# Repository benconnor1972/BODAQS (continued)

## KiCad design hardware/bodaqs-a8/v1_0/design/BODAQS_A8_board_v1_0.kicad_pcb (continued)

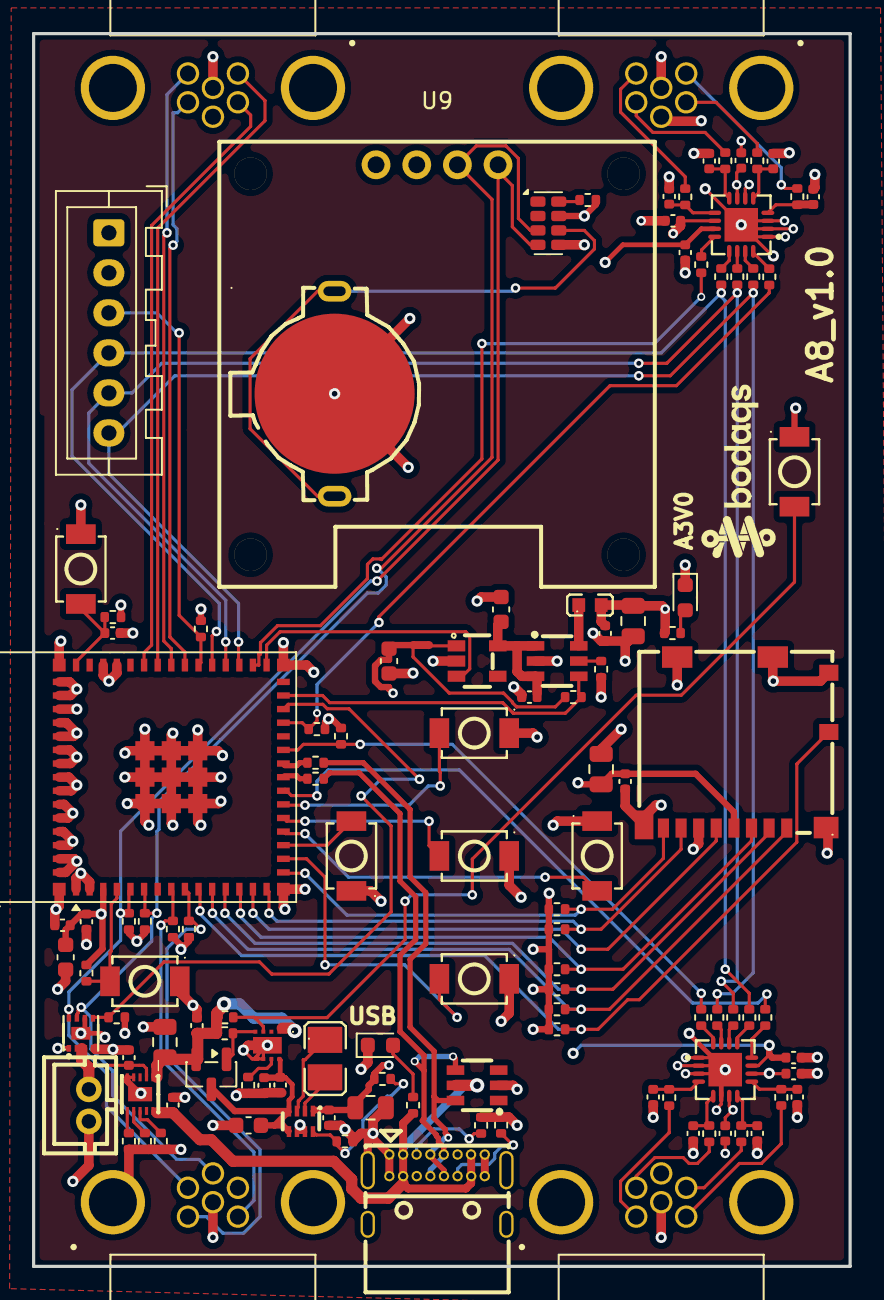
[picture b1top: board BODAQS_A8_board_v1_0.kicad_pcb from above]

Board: 4 copper layers, 51.0 x 77.0 mm, 120 parts (0 on the bottom side), 89 nets.

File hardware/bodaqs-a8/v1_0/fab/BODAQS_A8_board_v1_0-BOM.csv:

Designator,Footprint,Quantity,Value,LCSC Part #
BT1,BAT-TH_MY-1220-01,1,MY-1220-01,C964817
"C1, C10, C14, C15, C16, C18, C20, C29, C30, C31, C32, C7",0402,12,100nF,C1525
"C11, C33, C34, C6, C3",0402,4,1uF,C52923
"C12, C13",0603,2,2.2uF,C23630
"C17, C19, C9",0805,3,10uF,C15850
"C2, C8",0603,2,22uF,C84419
"C21, C22, C23, C24, C25, C26, C27, C28",0402,8,10nF,C15195
C4,0402,1,4.7uF,C23733
C5,0805,1,47uF,C16780
CN1,CONN-TH_B2B-PH-K-S,1,Battery,C131337
"D1, D2",0603,2,Red,C2286
IC1,XC6193AA05ERG,1,XC6193A103ER-G,C19267155
L1,L0603,1,MPZ1608S601ATA00,C107335
Q1,SOT-23,1,DMG2301L,C102619
"R1, R11, R13, R15, R22, R25, R26, R27, R28, R29, R30, R31, R4",0402,13,10k,C25744
"R10, R9",0402,2,22,C25092
R12,0402,1,511k,C64042
R14,0402,1,91k,C4147
R16,0402,1,18k,C25762
R17,0402,1,1k,C11702
"R18, R19, R3, R5, R7, R8",0402,6,4.7k,C25900
"R2, R6",0402,2,47k,C25792
"R20, R21, R23",0402,3,200k,C25764
R24,0402,1,133k,C25753
"R32, R33, R34, R35, R36, R37, R38, R39",0402,8,100R,C25076
"R40, R41, R42, R43, R44, R45, R46, R47, R48, R49",0402,10,47R,C25120
"R50, R51",0402,2,5.1k,C25905
SIM1,SIM-SMD_8P-1040310811,1,1040310811,C585350
"SW1, SW2, SW3, SW4, SW5, SW6, SW7, SW8",SW-SMD_L3.9-W3.0-P4.45,8,TS-1088-AR02016,C720477
U1,ESP32-S2-MINI-1,1,ESP32-S3-MINI,C3013941
"U10, U11",VQFN-16_L3.5-W3.5-P0.50-BL-EP2.1,2,ADS1220IRVAR,C2651338
U12,SOT-23-6_L2.9-W1.6-P0.95-LS2.8-BR,1,DT1042-04SO,C19626385
U2,L1008,1,DFE252012P-1R0M=P2,C882955
U3,TDFN-8_L2.0-W2.0-P0.50-BL-EP1.2,1,MAX17048G+T10,C2682616
U4,SOT-583-8_L2.1-W1.2-P0.50-LS1.6-BL,1,TPS631000DRLR,C5219190
U5,WSON-10_L2.2-W2.0-P0.40-BL-EP_TI_DLH0010A,1,BQ25185DLHR,C19725033
U6,TSOT-23-5_L2.9-W1.6-P0.95-LS2.8-BR,1,TPS7A2030PDBVR,C963429
U7,SOT-23-6_L2.9-W1.6-P0.95-LS2.8-BR,1,TPS2553DBVR,C55266
U8,MicroCrystal_C7_SON-8_1.5x3.2mm_P0.9mm,1,RV-3028-C7,C3019759
USB1,USC-C-SMD_USB4085-GF-A,1,USB4085-GF-A_C7095263,C7095263

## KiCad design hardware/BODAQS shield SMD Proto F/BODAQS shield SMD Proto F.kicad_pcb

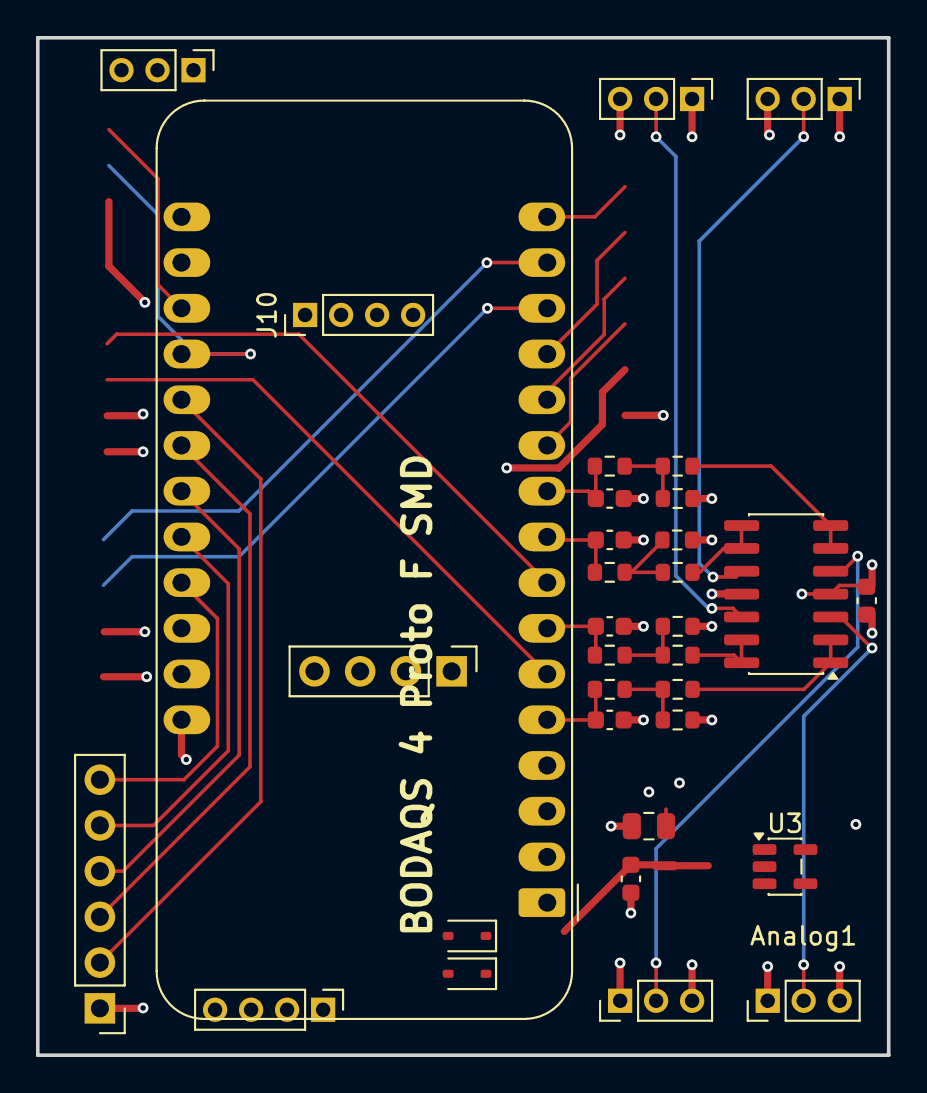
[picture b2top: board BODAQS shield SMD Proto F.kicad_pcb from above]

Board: 4 copper layers, 47.3 x 56.5 mm, 34 parts (0 on the bottom side), 37 nets.

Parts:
C2, C3, C5, C7: 10nF; C_0603_1608Metric
C9: 100nF; C_0603_1608Metric
C17: 2.2uF; C_0805_2012Metric
C21: 2.2uF; C_0603_1608Metric
D1, D2: BAT60A; D_SOD-323
J1: Analog1; PinHeader_1x03_P2.00mm_Vertical
J2: Analog2; PinHeader_1x03_P2.00mm_Vertical
J3: Analog3; PinHeader_1x03_P2.00mm_Vertical
J4: Analog4; PinHeader_1x03_P2.00mm_Vertical
J5: Bar; PinHeader_1x03_P2.00mm_Vertical
J6: I2C1; PinHeader_1x04_P2.00mm_Vertical
J7: UART; PinHeader_1x04_P2.54mm_Vertical
J8: Navigation; PinHeader_1x06_P2.54mm_Vertical
J10: I2C0; PinHeader_1x04_P2.00mm_Vertical
NT1: NetTie_2; NetTie-2_SMD_Pad0.5mm
R1, R4, R6, R8, R9, R10, R11, R12: 10K; R_0603_1608Metric
R2, R3, R5, R7: 68R; R_0603_1608Metric
U1: Adafruit_Feather
U2: MCP6004; SOIC-14_3.9x8.7mm_P1.27mm
U3: TPS7A2033PDBVR; SOT-23-5

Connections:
LED: J5.3, U1.19 (GPIO1)
TXO: J7.4, U1.15 (43/TX)
+3V3: J6.2, J7.1, J10.2, U1.2 (3.3V)
A3V3: C9.1, C17.1, J1.1, J2.1, J3.1, J4.1, U2.4 (V+), U3.5 (OUT)
ANALOG1: C2.1, R2.1, U1.5 (10/AN)
ANALOG2: C3.1, R3.1, U1.10 (18/AN)
ANALOG3: C5.1, R5.1, U1.9 (17/AN)
ANALOG4: C7.1, R7.1, U1.7 (15/AN)
Down: J8.5, U1.24 (GPIO7)
EN: U1.16 (GPIO42), U3.3 (EN)
Enter: J8.2, U1.21 (GPIO4)
GND: C2.2, C3.2, C5.2, C7.2, C9.2, C17.2, C21.2, J1.3, J2.3, J3.3, J4.3, J5.1, J6.1, J7.2, J8.1, J10.1, R9.1, R10.1, R11.1, R12.1, U1.4 (GND), U2.11 (V-), U3.2 (GND)
Left: J8.4, U1.23 (GPIO6)
Mark: J5.2, U1.20 (GPIO2)
unnamed: J1.2, U2.3 (+)
unnamed: J2.2, U2.5 (+)
unnamed: J3.2, U2.10 (+)
unnamed: J4.2, U2.12 (+)
unnamed: R1.1, R2.2, R9.2
unnamed: R3.2, R4.1, R10.2
unnamed: R5.2, R6.1, R11.2
unnamed: R7.2, R8.1, R12.2
unnamed: R1.2, U2.1, U2.2 (-)
unnamed: R4.2, U2.6 (-), U2.7
unnamed: R6.2, U2.8, U2.9 (-)
unnamed: R8.2, U2.13 (-), U2.14
unnamed: NT1.2, U3.1 (IN)
RXI: J7.3, U1.14 (44/RX)
Right: J8.3, U1.22 (GPIO5)
SCL0: J10.3, U1.18 (SCL/9)
SCL1: J6.3, U1.6 (14/AN)
SDA0: J10.4, U1.17 (SDA/8)
SDA1: J6.4, U1.8 (16/AN)
Up: J8.6, U1.25 (GPIO21)
VBAT: D1.2 (A), U1.28 (VBAT)
VIN: C21.1, D1.1 (K), D2.1 (K), NT1.1
VUSB: D2.2 (A), U1.26 (VUSB)

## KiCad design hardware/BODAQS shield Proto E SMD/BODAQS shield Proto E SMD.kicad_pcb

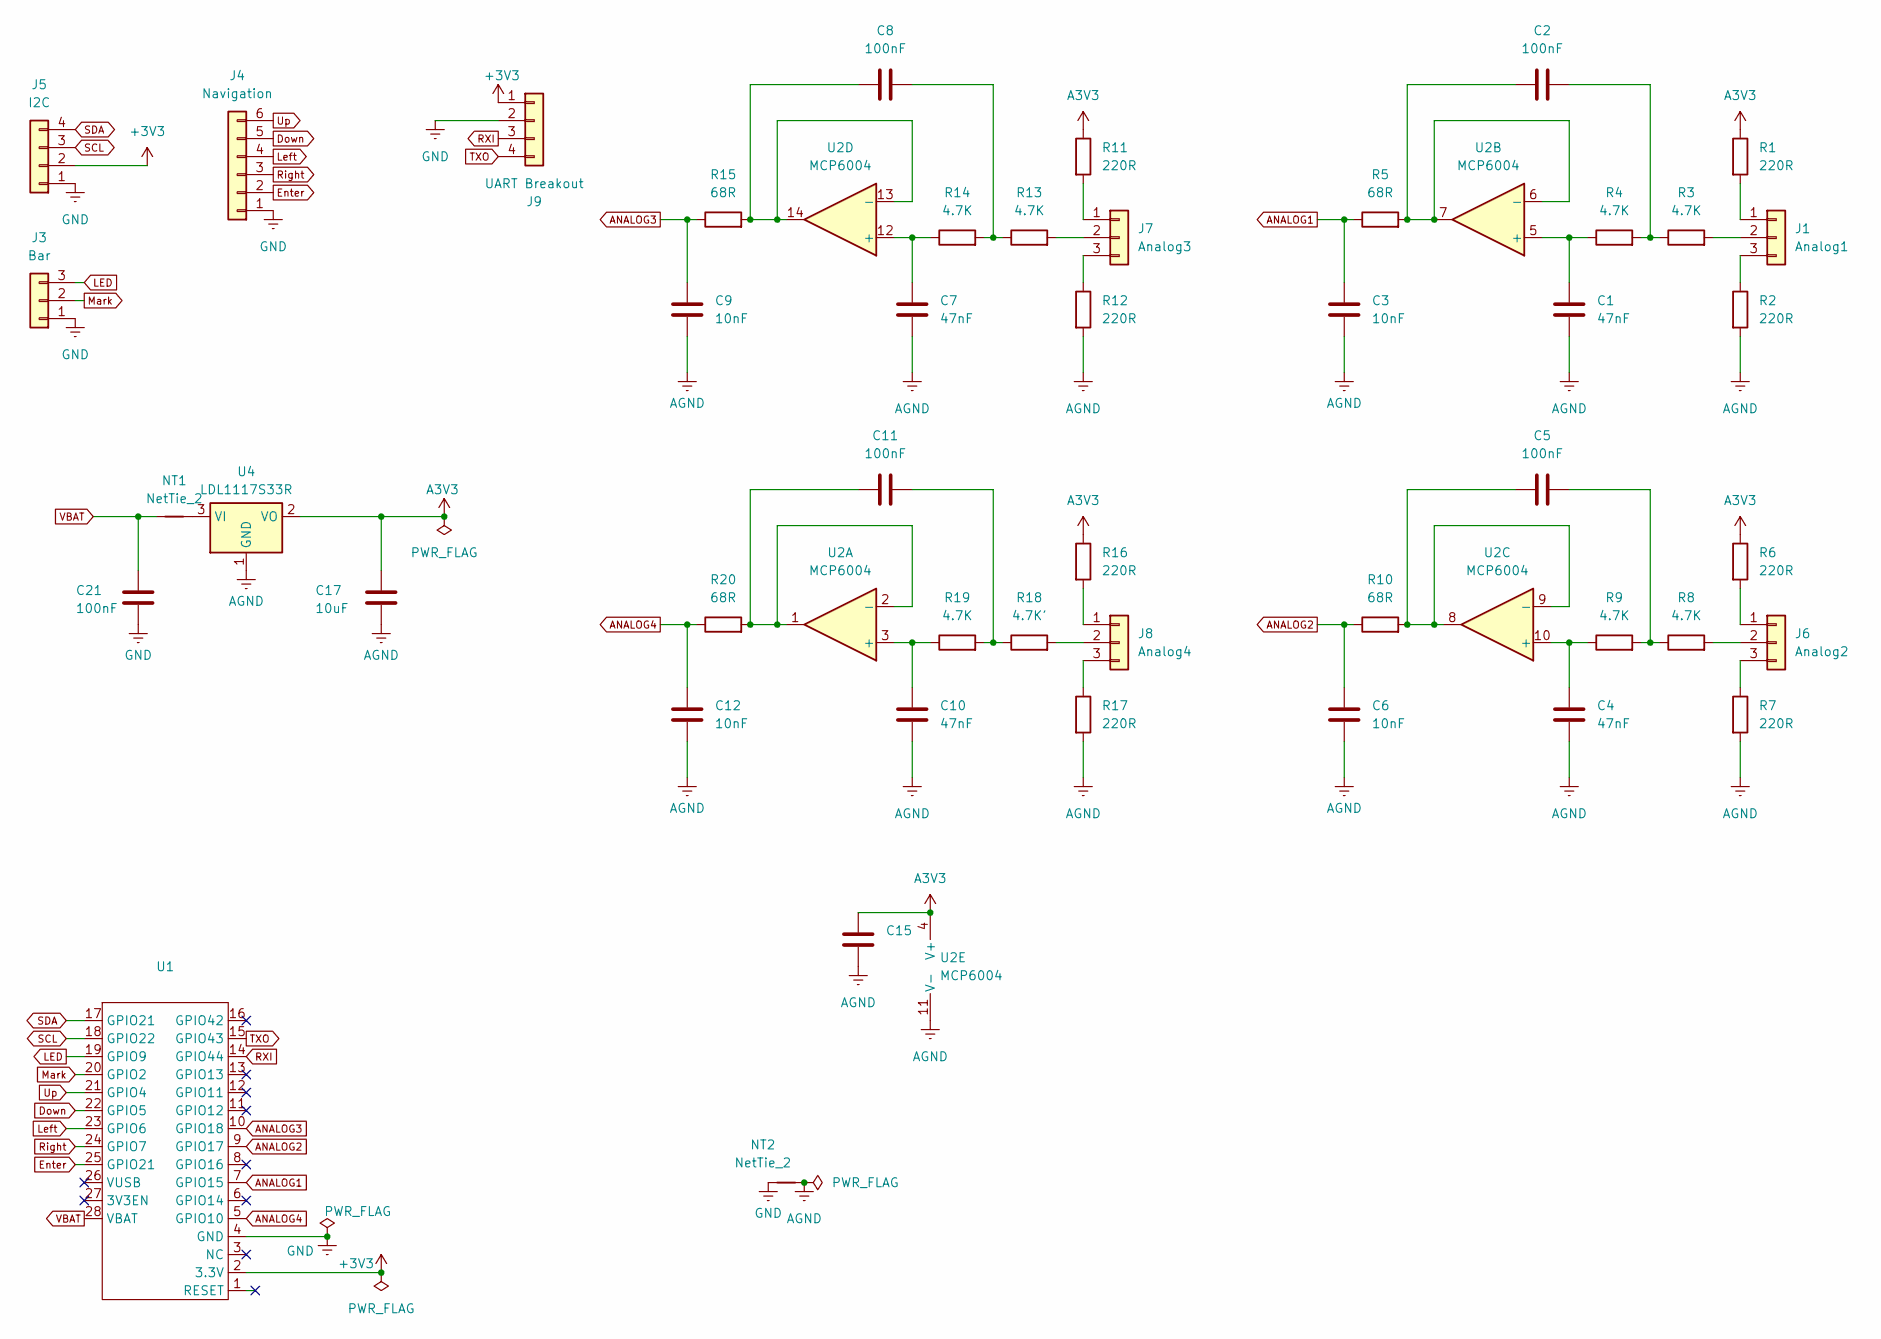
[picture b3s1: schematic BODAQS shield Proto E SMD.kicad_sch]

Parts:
C1, C4, C7, C10: 47nF; C_0603_1608Metric
C2, C5, C8, C11, C15, C21: 100nF; C_0603_1608Metric
C3, C6, C9, C12: 10nF; C_0603_1608Metric
C17: 10uF; C_0805_2012Metric
J1: Analog1; PinHeader_1x03_P2.00mm_Vertical
J3: Bar; PinHeader_1x03_P2.00mm_Vertical
J4: Navigation; PinHeader_1x06_P2.54mm_Vertical
J5: I2C; PinHeader_1x04_P2.00mm_Vertical
J6: Analog2; PinHeader_1x03_P2.00mm_Vertical
J7: Analog3; PinHeader_1x03_P2.00mm_Vertical
J8: Analog4; PinHeader_1x03_P2.00mm_Vertical
J9: UART Breakout; PinHeader_1x04_P2.54mm_Vertical
NT1, NT2: NetTie_2; NetTie-2_SMD_Pad0.5mm
R1, R2, R6, R7, R11, R12, R16, R17: 220R; R_0603_1608Metric
R3, R4, R8, R9, R13, R14, R19: 4.7K; R_0603_1608Metric
R5, R10, R15, R20: 68R; R_0603_1608Metric
R18: 4.7K'; R_0603_1608Metric
U1: Adafruit_Feather
U2: MCP6004; SOIC-14_3.9x8.7mm_P1.27mm
U4: LDL1117S33R; SOT-223-3_TabPin2

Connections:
LED: J3.3, U1.19 (GPIO9)
TXO: J9.4, U1.15 (GPIO43)
+3V3: J5.2, J9.1, U1.2 (3.3V)
A3V3: C15.1, C17.1, R1.1, R6.1, R11.1, R16.1, U2.4 (V+), U4.2 (VO)
AGND: C1.2, C3.2, C4.2, C6.2, C7.2, C9.2, C10.2, C12.2, C15.2, C17.2, NT2.2, R2.2, R7.2, R12.2, R17.2, U2.11 (V-), U4.1 (GND)
ANALOG1: C3.1, R5.1, U1.7 (GPIO15)
ANALOG2: C6.1, R10.1, U1.9 (GPIO17)
ANALOG3: C9.1, R15.1, U1.10 (GPIO18)
ANALOG4: C12.1, R20.1, U1.5 (GPIO10)
Down: J4.5, U1.22 (GPIO5)
Enter: J4.2, U1.25 (GPIO21)
GND: C21.2, J3.1, J4.1, J5.1, J9.2, NT2.1, U1.4 (GND)
Left: J4.4, U1.23 (GPIO6)
Mark: J3.2, U1.20 (GPIO2)
unnamed: C2.2, R3.1, R4.2
unnamed: C5.2, R8.1, R9.2
unnamed: C8.2, R13.1, R14.2
unnamed: C11.2, R18.1, R19.2
unnamed: J1.1, R1.2
unnamed: J1.2, R3.2
unnamed: J1.3, R2.1
unnamed: J6.1, R6.2
unnamed: J6.2, R8.2
unnamed: J6.3, R7.1
unnamed: J7.1, R11.2
unnamed: J7.2, R13.2
unnamed: J7.3, R12.1
unnamed: J8.1, R16.2
unnamed: J8.2, R18.2
unnamed: J8.3, R17.1
unnamed: C10.1, R19.1, U2.3 (+)
unnamed: C11.1, R20.2, U2.1, U2.2 (-)
unnamed: C1.1, R4.1, U2.5 (+)
unnamed: C2.1, R5.2, U2.6 (-), U2.7
unnamed: C4.1, R9.1, U2.10 (+)
unnamed: C5.1, R10.2, U2.8, U2.9 (-)
unnamed: C7.1, R14.1, U2.12 (+)
unnamed: C8.1, R15.2, U2.13 (-), U2.14
unnamed: NT1.2, U4.3 (VI)
RXI: J9.3, U1.14 (GPIO44)
Right: J4.3, U1.24 (GPIO7)
SCL: J5.3, U1.18 (GPIO22)
SDA: J5.4, U1.17 (GPIO21)
Up: J4.6, U1.21 (GPIO4)
VBAT: C21.1, NT1.1, U1.28 (VBAT)

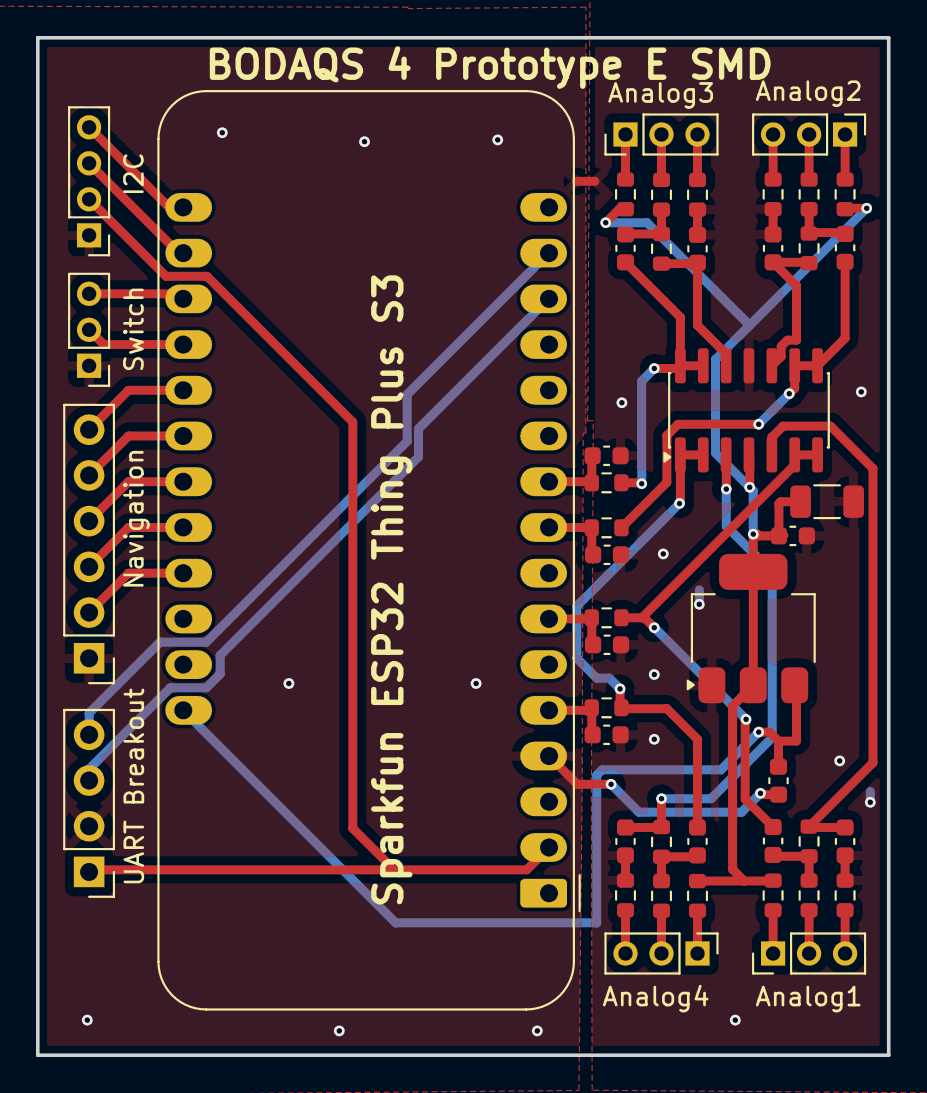
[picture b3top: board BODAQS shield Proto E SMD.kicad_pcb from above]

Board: 2 copper layers, 47.3 x 56.5 mm, 48 parts (0 on the bottom side), 45 nets.

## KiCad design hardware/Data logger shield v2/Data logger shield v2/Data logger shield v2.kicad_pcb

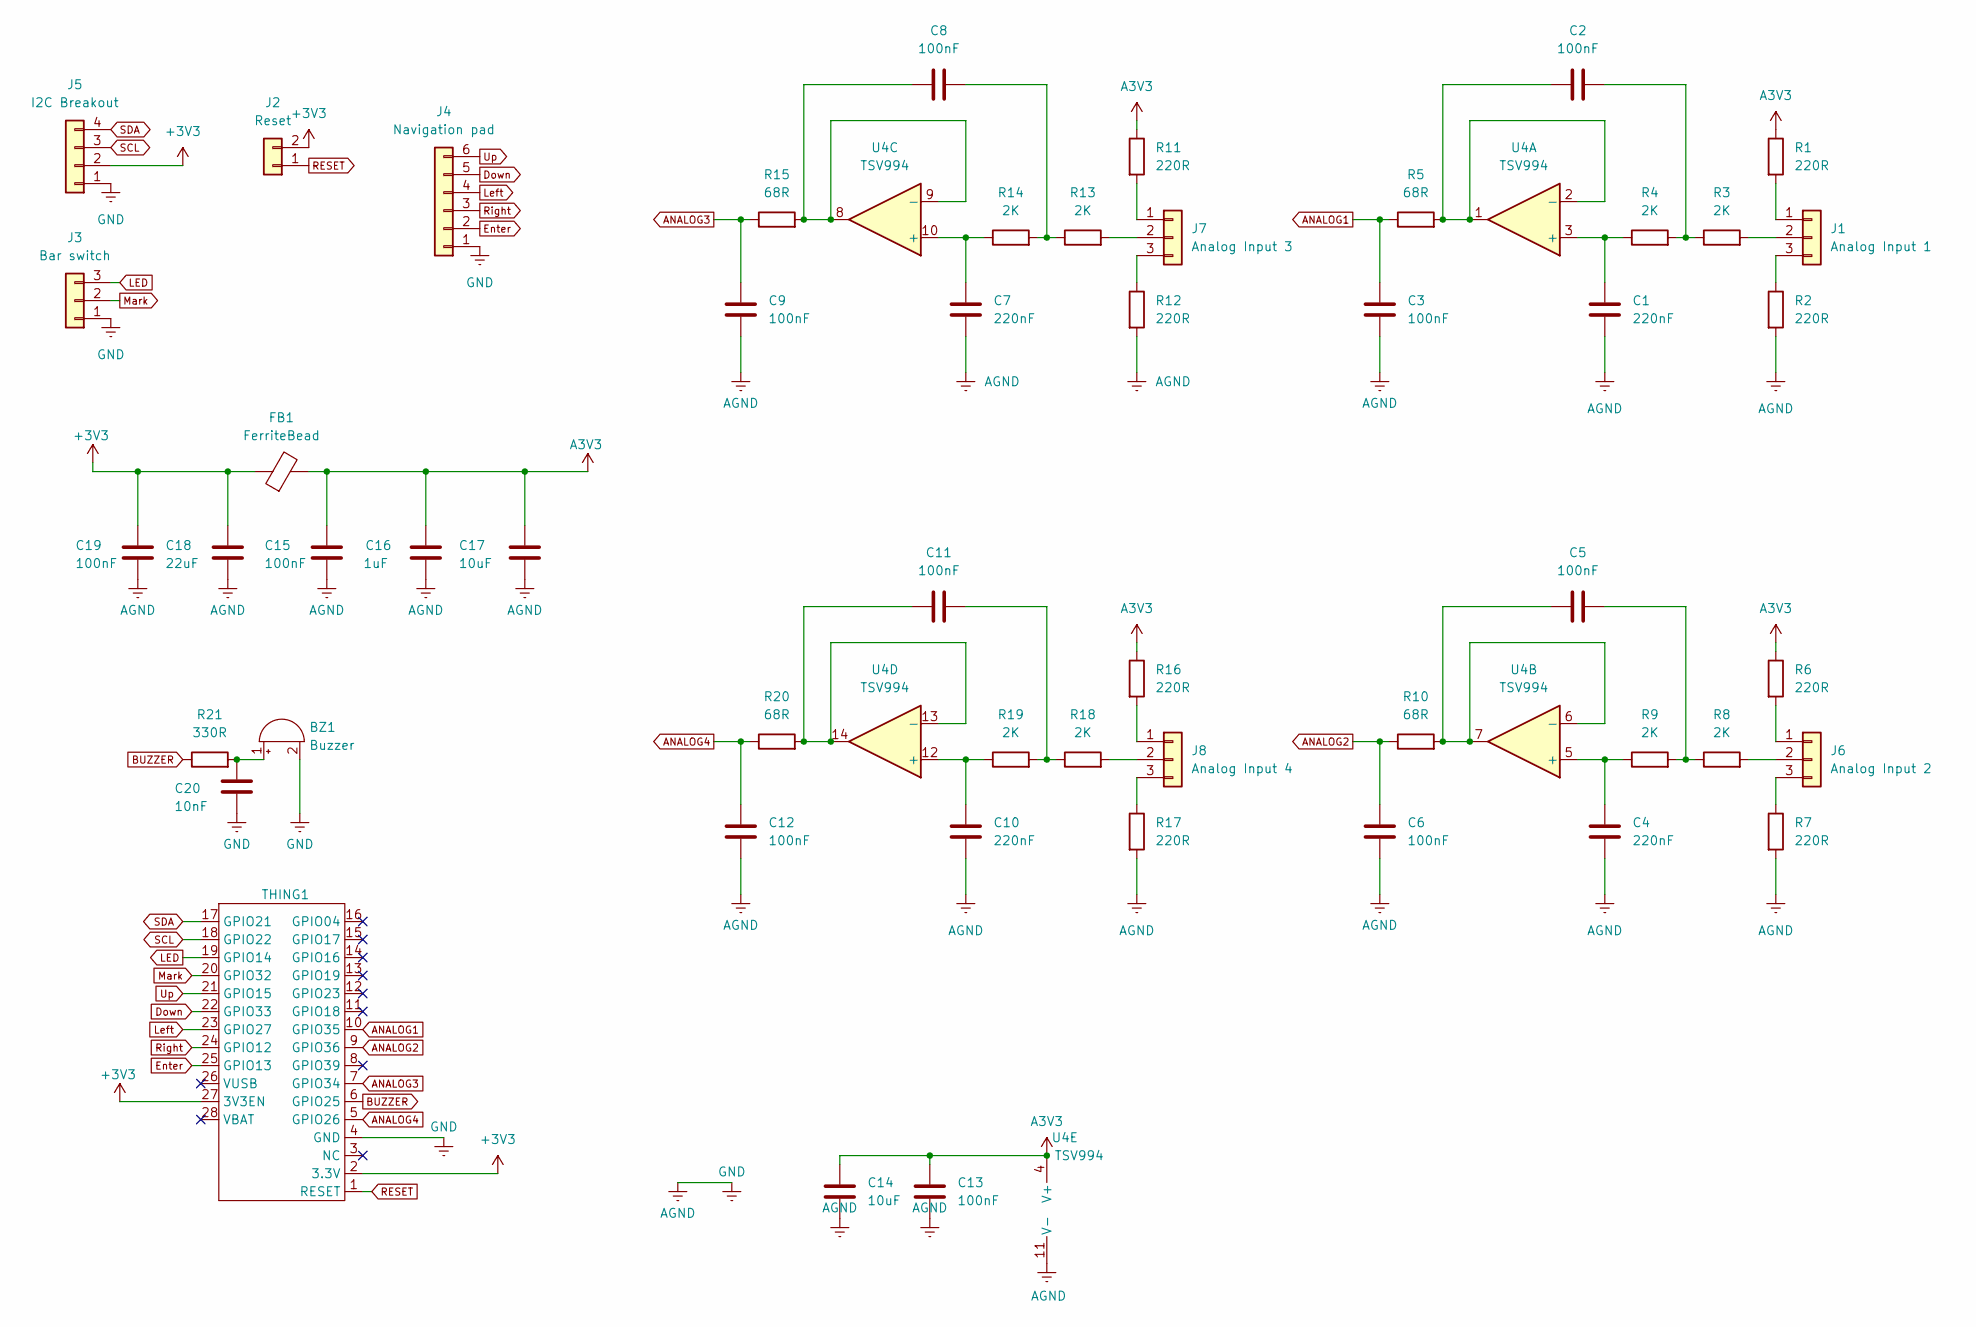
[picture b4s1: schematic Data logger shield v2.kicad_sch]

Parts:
BZ1: Buzzer; Buzzer_12x9.5RM7.6
C1, C4, C7, C10: 220nF; C_0603_1608Metric
C2, C3, C5, C6, C8, C9, C11, C12, C13, C15, C19: 100nF; C_0603_1608Metric
C14, C17: 10uF; C_0603_1608Metric
C16: 1uF; C_0603_1608Metric
C18: 22uF; C_0603_1608Metric
C20: 10nF; C_0603_1608Metric
FB1: FerriteBead; L_Axial_L11.0mm_D4.5mm_P15.24mm_Horizontal_Fastron_MECC
J1: Analog Input 1; JST_PH_B3B-PH-K_1x03_P2.00mm_Vertical
J2: Reset; JST_PH_B2B-PH-K_1x02_P2.00mm_Vertical
J3: Bar switch; JST_PH_B3B-PH-K_1x03_P2.00mm_Vertical
J4: Navigation pad; JST_XH_B6B-XH-AM_1x06_P2.50mm_Vertical
J5: I2C Breakout; JST_PH_B4B-PH-K_1x04_P2.00mm_Vertical
J6: Analog Input 2; JST_PH_B3B-PH-K_1x03_P2.00mm_Vertical
J7: Analog Input 3; JST_PH_B3B-PH-K_1x03_P2.00mm_Vertical
J8: Analog Input 4; JST_PH_B3B-PH-K_1x03_P2.00mm_Vertical
R1, R6, R11, R16: 220R; R_0603_1608Metric_Pad0.98x0.95mm_HandSolder
R2, R7, R12, R17: 220R; R_0603_1608Metric
R3, R4, R8, R9, R13, R14, R18, R19: 2K; R_0603_1608Metric
R5, R10, R15, R20: 68R; R_0603_1608Metric
R21: 330R; R_0603_1608Metric
THING1: Adafruit_Feather
U4: TSV994

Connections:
LED: J3.3, THING1.19 (GPIO14)
+3V3: C18.1, C19.1, FB1.1, J2.2, J5.2, THING1.2 (3.3V), THING1.27 (3V3EN)
A3V3: C13.1, C14.1, C15.1, C16.1, C17.1, FB1.2, R1.1, R6.1, R11.1, R16.1, U4.4 (V+)
AGND: BZ1.2 (-), C1.2, C3.2, C4.2, C6.2, C7.2, C9.2, C10.2, C12.2, C13.2, C14.2, C15.2, C16.2, C17.2, C18.2, C19.2, C20.2, J3.1, J4.1, J5.1, R2.2, R7.2, R12.2, R17.2, THING1.4 (GND), U4.11 (V-)
ANALOG1: C3.1, R5.1, THING1.10 (GPIO35)
ANALOG2: C6.1, R10.1, THING1.9 (GPIO36)
ANALOG3: C9.1, R15.1, THING1.7 (GPIO34)
ANALOG4: C12.1, R20.1, THING1.5 (GPIO26)
BUZZER: R21.1, THING1.6 (GPIO25)
Down: J4.5, THING1.22 (GPIO33)
Enter: J4.2, THING1.25 (GPIO13)
Left: J4.4, THING1.23 (GPIO27)
Mark: J3.2, THING1.20 (GPIO32)
unnamed: BZ1.1 (+), C20.1, R21.2
unnamed: C2.2, R3.1, R4.2
unnamed: C5.2, R8.1, R9.2
unnamed: C8.2, R13.1, R14.2
unnamed: C11.2, R18.1, R19.2
unnamed: J1.1, R1.2
unnamed: J1.2, R3.2
unnamed: J1.3, R2.1
unnamed: J6.1, R6.2
unnamed: J6.2, R8.2
unnamed: J6.3, R7.1
unnamed: J7.1, R11.2
unnamed: J7.2, R13.2
unnamed: J7.3, R12.1
unnamed: J8.1, R16.2
unnamed: J8.2, R18.2
unnamed: J8.3, R17.1
unnamed: C1.1, R4.1, U4.3 (+)
unnamed: C2.1, R5.2, U4.1, U4.2 (-)
unnamed: C4.1, R9.1, U4.5 (+)
unnamed: C5.1, R10.2, U4.6 (-), U4.7
unnamed: C7.1, R14.1, U4.10 (+)
unnamed: C8.1, R15.2, U4.8, U4.9 (-)
unnamed: C10.1, R19.1, U4.12 (+)
unnamed: C11.1, R20.2, U4.13 (-), U4.14
RESET: J2.1, THING1.1 (RESET)
Right: J4.3, THING1.24 (GPIO12)
SCL: J5.3, THING1.18 (GPIO22)
SDA: J5.4, THING1.17 (GPIO21)
Up: J4.6, THING1.21 (GPIO15)

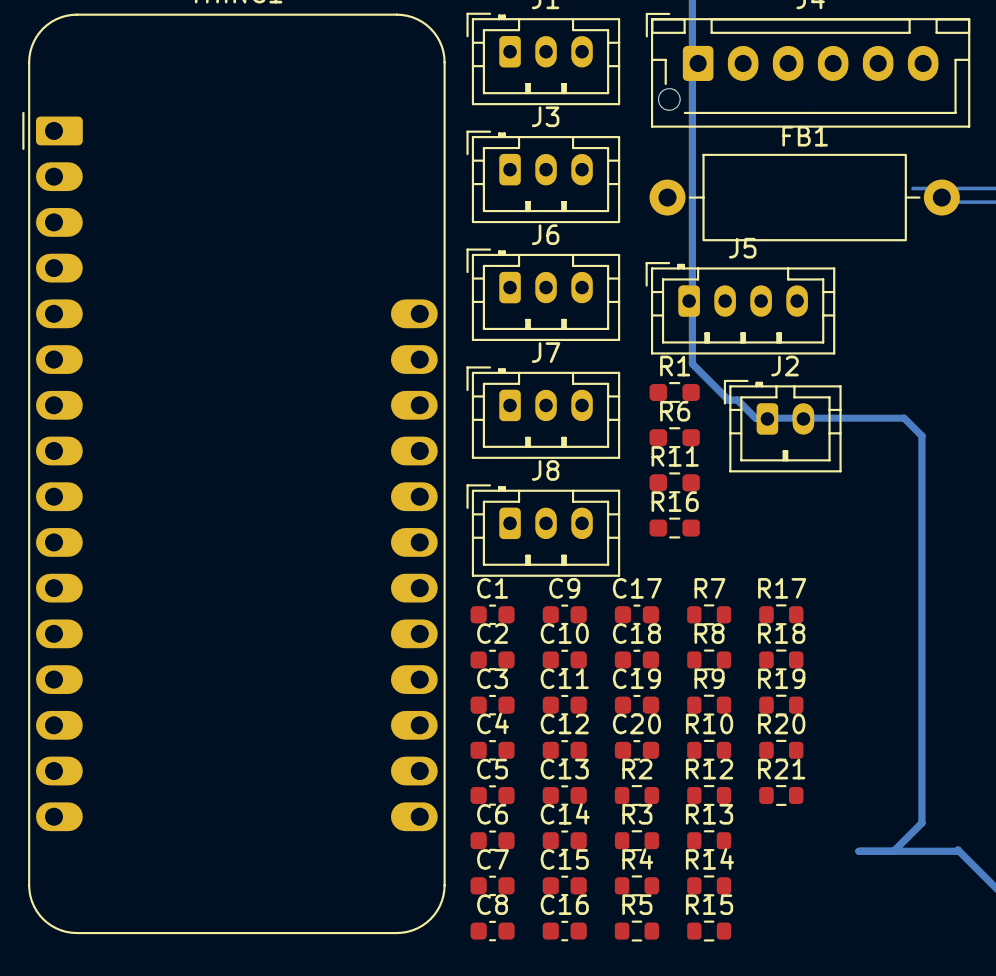
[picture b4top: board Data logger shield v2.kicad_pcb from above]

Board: 2 copper layers, 51 parts (0 on the bottom side), 43 nets.

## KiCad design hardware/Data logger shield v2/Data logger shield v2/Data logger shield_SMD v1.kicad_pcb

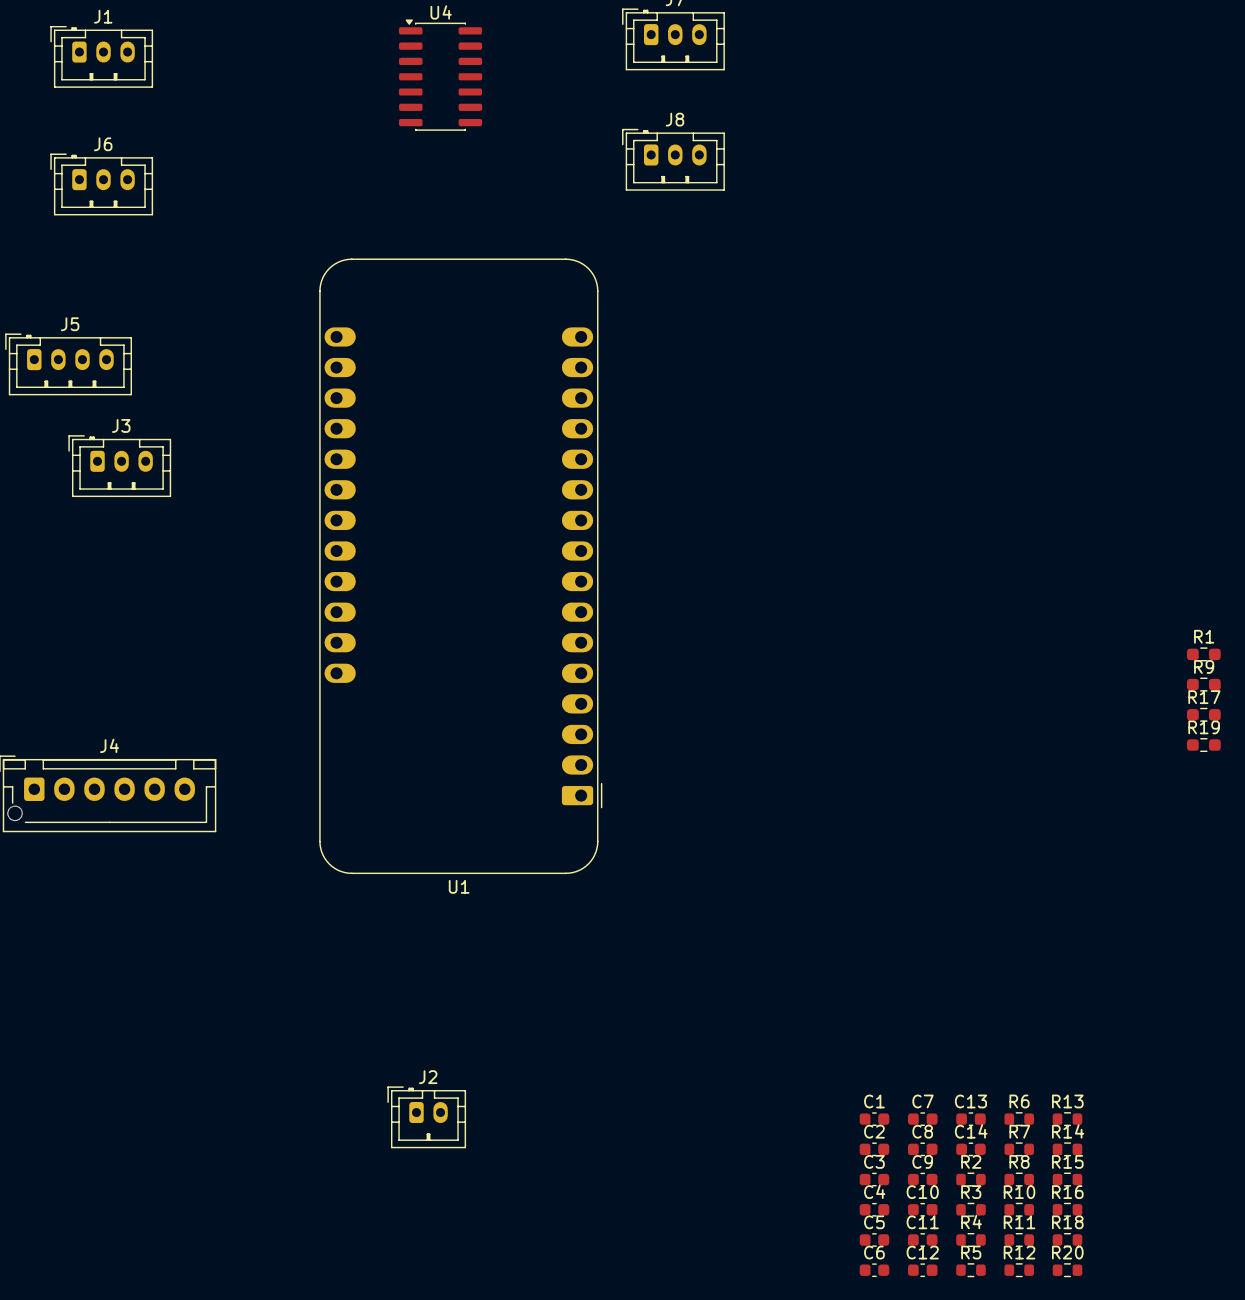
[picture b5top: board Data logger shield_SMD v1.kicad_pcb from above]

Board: 2 copper layers, 44 parts (0 on the bottom side), 40 nets, no tracks yet.

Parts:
C1, C6, C11, C12: 220nF; C_0603_1608Metric
C2, C3, C4, C5, C7, C8, C9, C10, C13: 100nF; C_0603_1608Metric
C14: 10uF; C_0603_1608Metric
J1, J6, J7, J8: Analog Input 1; JST_PH_B3B-PH-K_1x03_P2.00mm_Vertical
J2: Reset; JST_PH_B2B-PH-K_1x02_P2.00mm_Vertical
J3: Bar switch; JST_PH_B3B-PH-K_1x03_P2.00mm_Vertical
J4: Navigation pad; JST_XH_B6B-XH-AM_1x06_P2.50mm_Vertical
J5: I2C Breakout; JST_PH_B4B-PH-K_1x04_P2.00mm_Vertical
R1, R9, R17, R19: 220R; R_0603_1608Metric_Pad0.98x0.95mm_HandSolder
R2, R10, R18, R20: 220R; R_0603_1608Metric
R3, R4, R7, R8, R13, R14, R15, R16: 2K; R_0603_1608Metric
R5, R6, R11, R12: 68R; R_0603_1608Metric
U1: Adafruit_Feather
U4: TSV994; SOIC-14_3.9x8.7mm_P1.27mm

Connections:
LED: J3.3, U1.19 (GPIO14)
+3V3: J2.2, J5.2, R1.1, R9.1, R17.1, R19.1, U1.2 (3.3V), U1.27 (3V3EN), U4.4 (V+)
ANALOG1: C3.1, C7.1, R5.1, R11.1, U1.10 (GPIO35)
ANALOG3: C4.1, R6.1, U1.7 (GPIO34)
ANALOG4: C8.1, R12.1, U1.5 (GPIO26)
Down: J4.5, U1.22 (GPIO33)
Enter: J4.2, U1.25 (GPIO13)
GND: C1.2, C3.2, C4.2, C6.2, C7.2, C8.2, C11.2, C12.2, C13.2, C14.2, J3.1, J4.1, J5.1, R2.2, R10.2, R18.2, R20.2, U1.4 (GND), U4.11 (V-)
Left: J4.4, U1.23 (GPIO27)
Mark: J3.2, U1.20 (GPIO32)
unnamed: C2.2, R3.1, R4.2
unnamed: C5.2, R7.2, R8.1
unnamed: C9.2, R13.2, R15.1
unnamed: C10.2, R14.2, R16.1
unnamed: C13.1, C14.1
unnamed: J1.1, R1.2
unnamed: J1.2, R3.2
unnamed: J1.3, R2.1
unnamed: J6.1, R9.2
unnamed: J6.2, R8.2
unnamed: J6.3, R10.1
unnamed: J7.1, R17.2
unnamed: J7.2, R15.2
unnamed: J7.3, R18.1
unnamed: J8.1, R19.2
unnamed: J8.2, R16.2
unnamed: J8.3, R20.1
unnamed: C1.1, R4.1, U4.3 (+)
unnamed: C2.1, R5.2, U4.1, U4.2 (-)
unnamed: C6.1, R7.1, U4.5 (+)
unnamed: C5.1, R6.2, U4.6 (-), U4.7
unnamed: C11.1, R13.1, U4.10 (+)
unnamed: C9.1, R11.2, U4.8, U4.9 (-)
unnamed: C12.1, R14.1, U4.12 (+)
unnamed: C10.1, R12.2, U4.13 (-), U4.14
RESET: J2.1, U1.1 (RESET)
Right: J4.3, U1.24 (GPIO12)
SCL: J5.3, U1.18 (GPIO22)
SDA: J5.4, U1.17 (GPIO21)
Up: J4.6, U1.21 (GPIO15)

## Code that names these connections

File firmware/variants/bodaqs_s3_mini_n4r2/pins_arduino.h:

#ifndef Pins_Arduino_h
#define Pins_Arduino_h

#include <stdint.h>

#define USB_VID          0x303A
#define USB_PID          0x1001
#define USB_MANUFACTURER "BODAQS"
#define USB_PRODUCT      "BODAQS A8"
#define USB_SERIAL       ""

static const uint8_t TX = 43;
static const uint8_t RX = 44;
#define TX1 TX
#define RX1 RX

static const uint8_t SDA = 1;
static const uint8_t SCL = 2;

#define WIRE1_PIN_DEFINED 1
static const uint8_t SDA1 = 4;
static const uint8_t SCL1 = 5;

static const uint8_t SS   = 47;
static const uint8_t MOSI = 38;
static const uint8_t MISO = 39;
static const uint8_t SCK  = 37;

static const uint8_t CS0 = 47;
static const uint8_t CS1 = 21;
static const uint8_t CS2 = 40;

static const uint8_t SDIO_DET = 6;
static const uint8_t SDIO2    = 7;
static const uint8_t SDIO3    = 8;
static const uint8_t SDIO_CMD = 9;
static const uint8_t SDIO_CLK = 10;
static const uint8_t SDIO0    = 11;
static const uint8_t SDIO1    = 12;

static const uint8_t BTN_DOWN  = 13;
static const uint8_t BTN_LEFT  = 14;
static const uint8_t BTN_RIGHT = 15;
static const uint8_t BTN_ENTER = 16;
static const uint8_t BTN_UP    = 17;
static const uint8_t BTN_MARK  = 42;

static const uint8_t DRDY0 = 36;
static const uint8_t DRDY1 = 18;

static const uint8_t ANALOG_ENABLE = 35;
static const uint8_t MAX17048_ALRT = 33;
static const uint8_t TPS2553_A_FLT = 34;

#endif /* Pins_Arduino_h */
